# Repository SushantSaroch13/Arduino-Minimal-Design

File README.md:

# Arduino Minimal Design

A **minimal Arduino-compatible board** built around the **ATmega328P-M** microcontroller with an integrated **CH340E USB-to-Serial interface** for direct programming via USB.

The goal of this project is to demonstrate a **compact and practical Arduino hardware implementation** using minimal components while maintaining full functionality.

---

## Features

* ATmega328P based Arduino-compatible design
* Integrated **CH340E USB-to-UART** converter
* **Micro USB programming interface**
* 16 MHz crystal oscillator
* On-board **TX/RX status LEDs**
* Compact PCB layout with minimal components

---

## Hardware Architecture

The board consists of four main functional blocks:

**1. Microcontroller**

* ATmega328P-M
* External 16 MHz crystal
* Reset circuit

**2. USB Interface**

* CH340E USB to UART converter
* Micro USB connector

**3. Power Regulation**

* LM1117-3.3 linear regulator
* Input protection and filtering

**4. Status Indicators**

* Power LED
* TX/RX communication LEDs

---

## Schematic & PCB Layout

---

## 3D View

---

## Bill of Materials (BOM)

| Component           | Description                        | Qty |
| ------------------- | ---------------------------------- | --- |
| ATmega328P-M        | Microcontroller                    | 1   |
| CH340E              | USB to UART Converter              | 1   |
| LM1117DT-3.3        | Voltage Regulator                  | 1   |
| 16 MHz Crystal      | Clock Source                       | 1   |
| USB Micro Connector | Programming Interface              | 1   |
| Polyfuse            | USB Protection                     | 1   |
| SM4001              | Protection Diode                   | 1   |
| Reset Switch        | Push Button Reset                  | 1   |
| LEDs                | Power / TX / RX Indicators         | 4   |
| Resistors           | Various (330Ω, 1kΩ, 1k2Ω, 1MΩ)     | 9   |
| Capacitors          | Various (22pF, 100nF, 10uF, 100uF) | 10  |
| Pin Headers         | I/O Connections                    | 3   |

---

## Programming

The board can be programmed directly through the **USB interface**.

Steps:

1. Connect the board via **Micro USB**
2. Install **CH340 driver** (if not already installed)
3. Open **Arduino IDE**
4. Select **Arduino Uno / ATmega328P**
5. Choose the correct **COM port**
6. Upload your sketch

---

## Applications

This board can be used for:

* Embedded system prototyping
* IoT projects
* Arduino-based hardware development
* Learning **custom PCB design for microcontrollers**

---

## Tools Used

* **KiCad** – Schematic and PCB design
* **Arduino IDE** – Firmware programming

---

## Author

**Sushant Saroch**
Electronics & Communication Engineer
Focus: Embedded Systems • PCB Design • Hardware Development

---

⭐ If you find this project useful, consider starring the repository.

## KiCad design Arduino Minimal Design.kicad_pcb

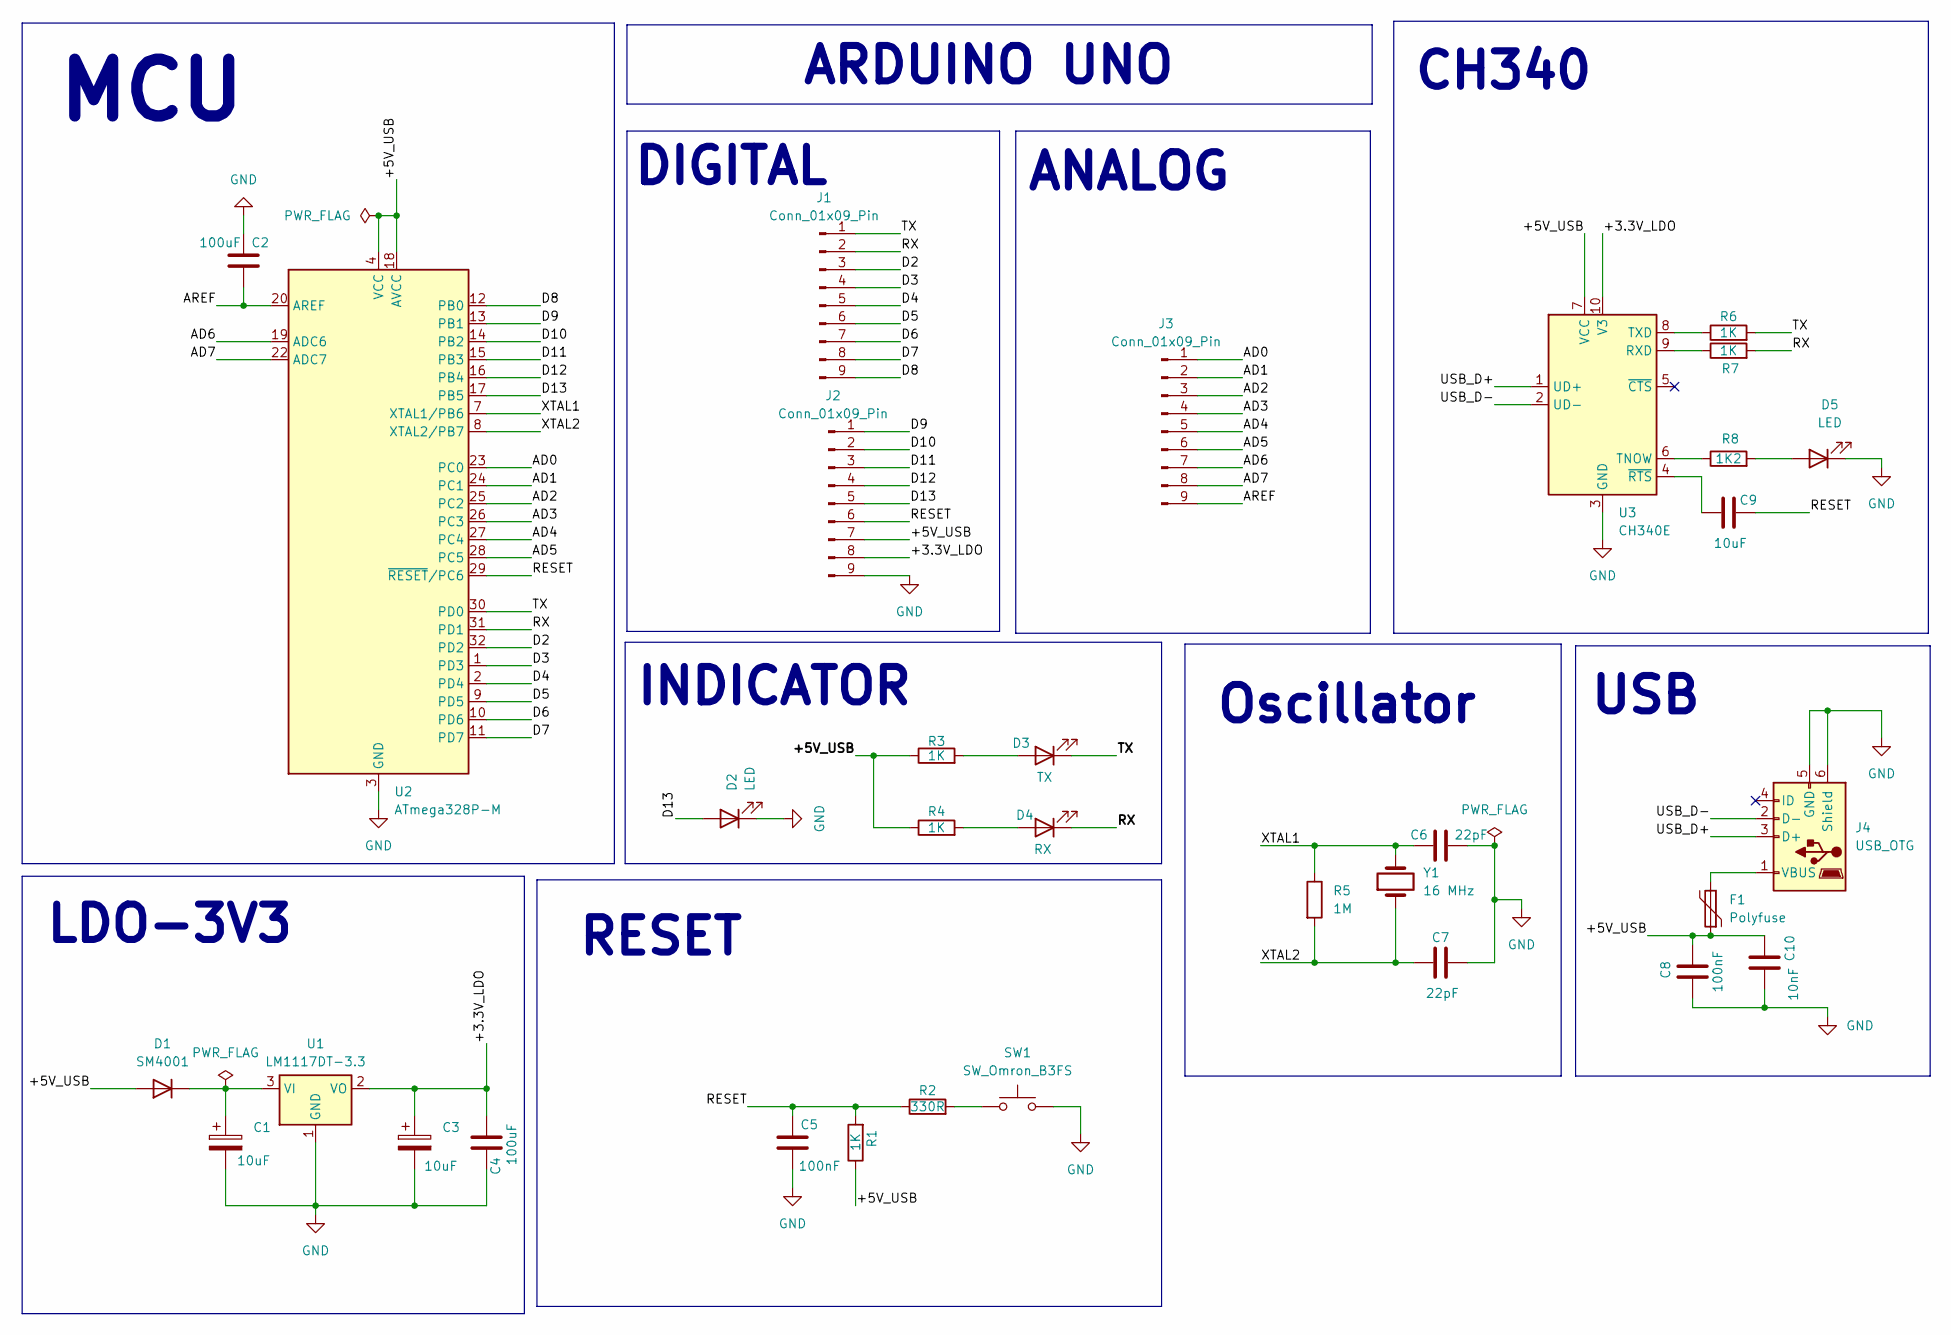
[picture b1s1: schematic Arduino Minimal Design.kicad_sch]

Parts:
C1, C3: 10uF; CP_EIA-3216-12_Kemet-S_HandSolder
C2, C4: 100uF; C_0805_2012Metric
C5, C8: 100nF; C_0805_2012Metric
C6, C7: 22pF; C_0805_2012Metric
C9: 10uF; C_0805_2012Metric
C10: 10nF; C_0805_2012Metric
D1: SM4001; D_MELF
D2, D5: LED; LED_0805_2012Metric
D3: TX; LED_0805_2012Metric
D4: RX; LED_0805_2012Metric
F1: Polyfuse; Fuse_0805_2012Metric
J1, J2, J3: Conn_01x09_Pin; PinHeader_1x09_P2.54mm_Vertical
J4: USB_OTG; USB_Micro-AB_Molex_47590-0001
R1, R3, R4, R6, R7: 1K; R_0805_2012Metric
R2: 330R; R_0805_2012Metric
R5: 1M; R_0805_2012Metric
R8: 1K2; R_0805_2012Metric
SW1: SW_Omron_B3FS; SW_SPST_Omron_B3FS-100xP
U1: LM1117DT-3.3; TO-252-3_TabPin2
U2: ATmega328P-M; QFN-32-1EP_5x5mm_P0.5mm_EP3.1x3.1mm
U3: CH340E; MSOP-10_3x3mm_P0.5mm
Y1: 16 MHz; Crystal_HC18-U_Vertical

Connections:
/+3.3V_LDO: C3.1, C4.1, J2.8, U1.2 (VO), U3.10 (V3)
/+5V_USB: C8.2, C10.2, D1.2 (A), F1.1, J2.7, R1.1, R3.1, R4.1, U2.4 (VCC), U2.6 (VCC), U2.18 (AVCC), U3.7 (VCC)
/AD0: J3.1, U2.23 (PC0)
/AD1: J3.2, U2.24 (PC1)
/AD2: J3.3, U2.25 (PC2)
/AD3: J3.4, U2.26 (PC3)
/AD4: J3.5, U2.27 (PC4)
/AD5: J3.6, U2.28 (PC5)
/AD6: J3.7, U2.19 (ADC6)
/AD7: J3.8, U2.22 (ADC7)
/AREF: C2.2, J3.9, U2.20 (AREF)
/D2: J1.3, U2.32 (PD2)
/D3: J1.4, U2.1 (PD3)
/D4: J1.5, U2.2 (PD4)
/D5: J1.6, U2.9 (PD5)
/D6: J1.7, U2.10 (PD6)
/D7: J1.8, U2.11 (PD7)
/D8: J1.9, U2.12 (PB0)
/D9: J2.1, U2.13 (PB1)
/D10: J2.2, U2.14 (PB2)
/D11: J2.3, U2.15 (PB3)
/D12: J2.4, U2.16 (PB4)
/D13: D2.2 (A), J2.5, U2.17 (PB5)
/RESET: C5.1, C9.2, J2.6, R1.2, R2.1, U2.29 (~RESET/PC6)
/RX: D4.1 (K), J1.2, R7.2, U2.31 (PD1)
/TX: D3.1 (K), J1.1, R6.2, U2.30 (PD0)
/USB_D+: J4.3 (D+), U3.1 (UD+)
/USB_D-: J4.2 (D-), U3.2 (UD-)
/XTAL1: C6.1, R5.1, U2.7 (XTAL1/PB6), Y1.2
/XTAL2: C7.1, R5.2, U2.8 (XTAL2/PB7), Y1.1
GND: C1.2, C2.1, C3.2, C4.2, C5.2, C6.2, C7.2, C8.1, C10.1, D2.1 (K), D5.1 (K), J2.9, J4.5 (GND), J4.6 (Shield), SW1.2, U1.1 (GND), U2.3 (GND), U2.5 (GND), U2.21 (GND), U2.33 (GND), U3.3 (GND)
unnamed: C1.1, D1.1 (K), U1.3 (VI)
unnamed: D3.2 (A), R3.2
unnamed: D4.2 (A), R4.2
unnamed: D5.2 (A), R8.2
unnamed: F1.2, J4.1 (VBUS)
unnamed: R2.2, SW1.1
unnamed: R7.1, U3.9 (RXD)
unnamed: R8.1, U3.6 (TNOW)
unnamed: R6.1, U3.8 (TXD)
unnamed: C9.1, U3.4 (~RTS)

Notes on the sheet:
ANALOG
DIGITAL
Oscillator
INDICATOR
LDO-3V3
USB
MCU
CH340
RESET
ARDUINO UNO

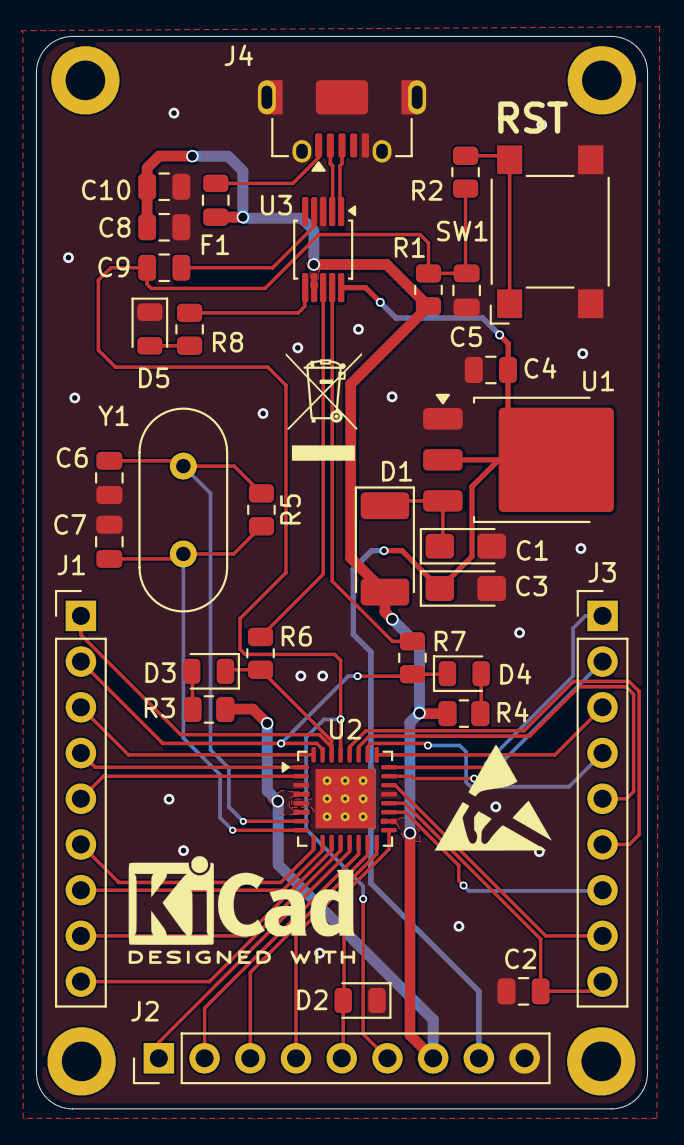
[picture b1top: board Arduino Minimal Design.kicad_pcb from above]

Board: 2 copper layers, 33.9 x 59.6 mm, 33 parts (0 on the bottom side), 41 nets.

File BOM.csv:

"Id";"Designator";"Footprint";"Quantity";"Designation";"Supplier and ref";
1;"Y1";"Crystal_HC49-4H_Vertical";1;"16 MHz";;;
2;"U1";"TO-252-3_TabPin2";1;"LM1117DT-3.3";;;
3;"D2,D5";"LED_0805_2012Metric";2;"LED";;;
4;"J3,J2,J1";"PinHeader_1x09_P2.54mm_Vertical";3;"Conn_01x09_Pin";;;
5;"D4";"LED_0805_2012Metric";1;"RX";;;
6;"J4";"USB_Micro-AB_Molex_47590-0001";1;"USB_OTG";;;
7;"U3";"MSOP-10_3x3mm_P0.5mm";1;"CH340E";;;
8;"C10";"C_0805_2012Metric";1;"10nF";;;
9;"C7,C6";"C_0805_2012Metric";2;"22pF";;;
10;"R3,R1,R4,R7,R6";"R_0805_2012Metric";5;"1K";;;
11;"SW1";"SW_SPST_Omron_B3FS-100xP";1;"SW_Omron_B3FS";;;
12;"R5";"R_0805_2012Metric";1;"1M";;;
13;"C4,C2";"C_0805_2012Metric";2;"100uF";;;
14;"C8,C5";"C_0805_2012Metric";2;"100nF";;;
15;"C3,C1";"CP_EIA-3216-12_Kemet-S_HandSolder";2;"10uF";;;
16;"U2";"QFN-32-1EP_5x5mm_P0.5mm_EP3.3x3.3mm_ThermalVias";1;"ATmega328P-M";;;
17;"R8";"R_0805_2012Metric";1;"1K2";;;
18;"C9";"C_0805_2012Metric";1;"10uF";;;
19;"D1";"D_MELF";1;"SM4001";;;
20;"R2";"R_0805_2012Metric";1;"330R";;;
21;"F1";"Fuse_0805_2012Metric";1;"Polyfuse";;;
22;"D3";"LED_0805_2012Metric";1;"TX";;;

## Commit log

2026-03-13 Adding Images
